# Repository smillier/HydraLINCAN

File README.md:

# HydraLINCAN shield for HydraBus

CAN and LIN Bus shield for Hydrabus http://hydrabus.com/
Refer to Hydrabus Wiki for more information on usage. https://github.com/hydrabus/hydrafw/wiki/HydraFW-CAN-guide

#### New version with cleaner and easier to read silkscreen.

Here is the wiring schema for HydraLINCAN.

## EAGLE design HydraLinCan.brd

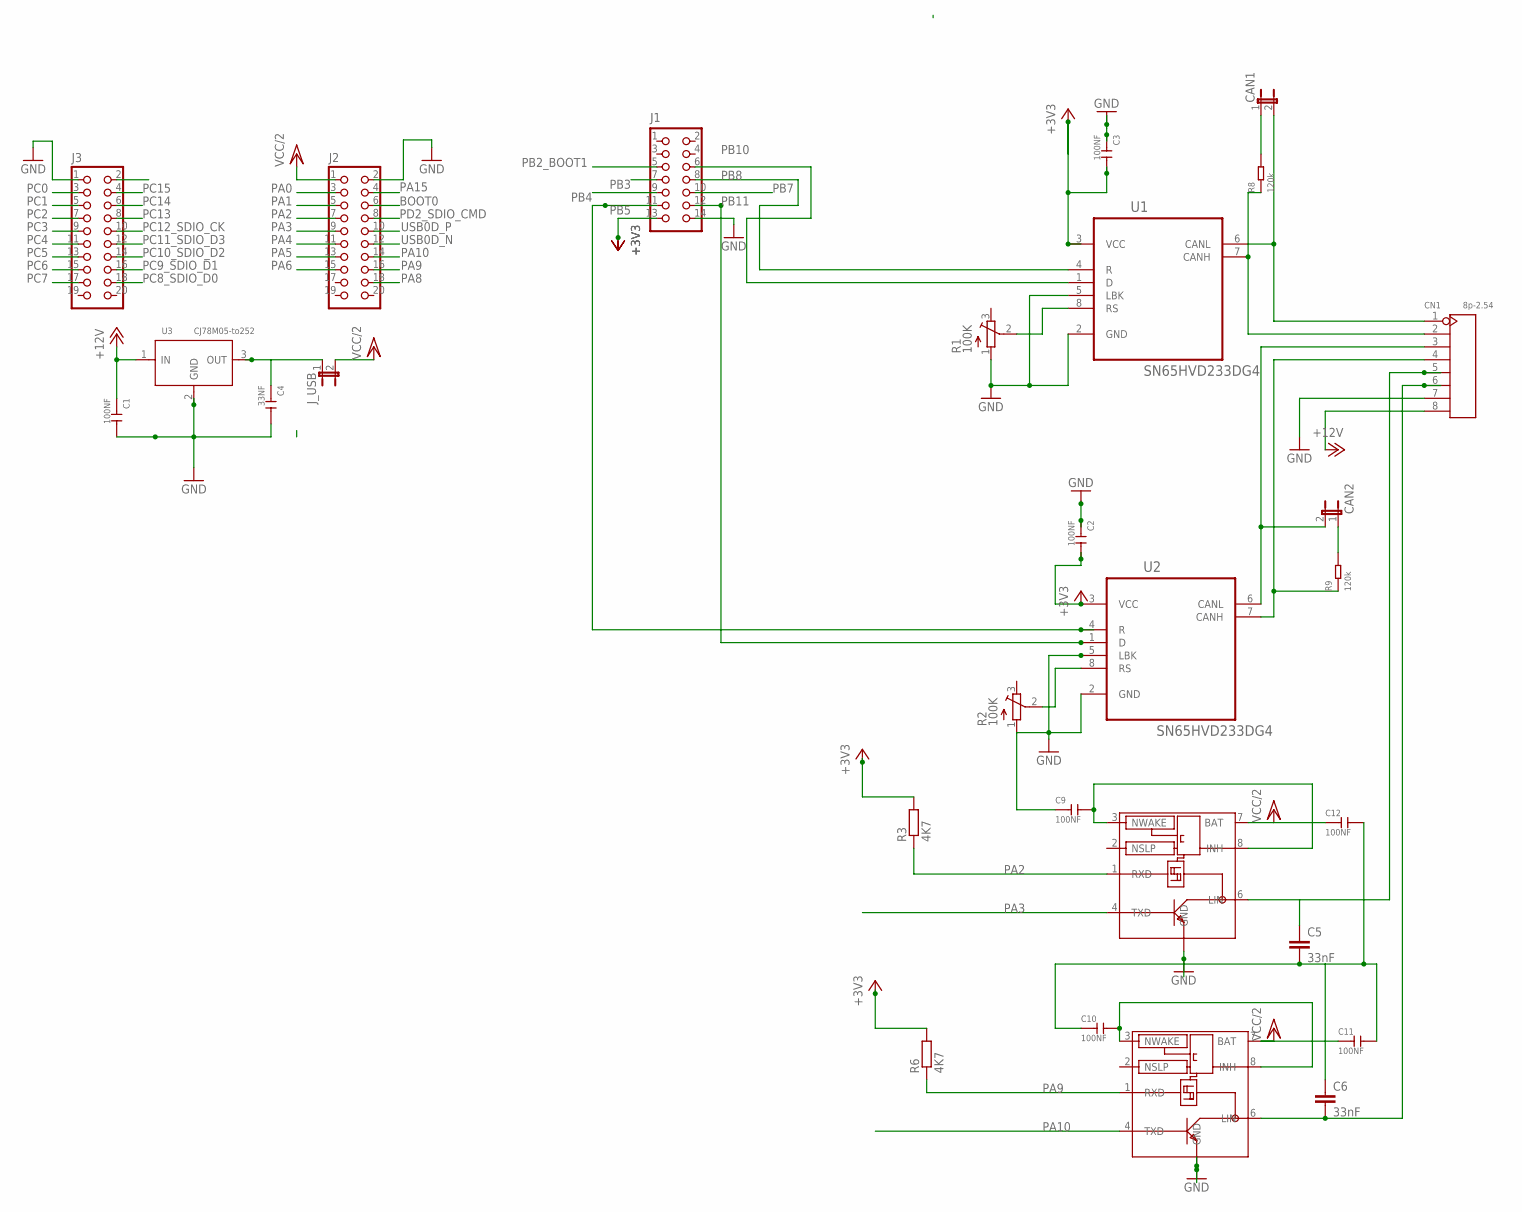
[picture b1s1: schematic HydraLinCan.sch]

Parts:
C1, C2, C3, C9, C10, C11, C12: 100NF; C0805
C4: 33NF; C0805
C5, C6: 33nF; 1206
CAN1, CAN2: JP1E; JP1
CN1: 8p-2.54; H8-2.54
J1: HYDRABUS_SHIELD_CON_HEADER_2X07; HYDRABUS_SHIELD_M2X7
J2, J3: HYDRABUS_SHIELD_CON_HEADER_2X10; HYDRABUS_SHIELD_M2X10
J_USB: JP1E; JP1
LIN1, LIN2: TJA1021SO8; SO8
R1, R2: 100K; SM-42/43A
R3, R6: 4K7; M1206
R8, R9: 120k; R1206
U1, U2: SN65HVD233DG4; SOIC127P600X175-8N
U3: CJ78M05-to252; TO-252

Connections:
+3V3: C2.2, C3.2, J1.13, R3.2, R6.2, U1.3 (VCC), U2.3 (VCC)
+12V: C1.1, CN1.8, U3.1 (IN)
BOOT0: J2.6
CAN1_N: CAN1.2, CN1.1, U1.6 (CANL)
CAN1_P: CN1.2, R8.1, U1.7 (CANH)
CAN2_N: CAN2.2, CN1.3, U2.6 (CANL)
CAN2_P: CN1.4, R9.1, U2.7 (CANH)
GND: C1.2, C2.1, C3.1, C4.2, C5.2, C6.1, C10.1, C11.2, C12.2, CN1.7, J1.14, J2.2, J3.1, LIN1.5 (GND), LIN2.5 (GND), R1.1 (A), U1.2 (GND), U1.5 (LBK), U2.5 (LBK), U3.2 (GND)
unnamed: R1.2 (S), U1.8 (RS)
unnamed: C5.1, CN1.5, LIN1.6 (LIN)
unnamed: C6.2, CN1.6, LIN2.6 (LIN)
unnamed: C9.2, LIN1.3 (NWAKE), LIN1.8 (INH)
unnamed: C10.2, LIN2.3 (NWAKE), LIN2.8 (INH)
unnamed: C9.1, R2.1 (A), U2.2 (GND)
unnamed: C4.1, J_USB.1, U3.3 (OUT)
unnamed: CAN2.1, R9.2
unnamed: R2.2 (S), U2.8 (RS)
unnamed: CAN1.1, R8.2
PA0: J2.3
PA1: J2.5
PA2: J2.7, LIN1.1 (RXD), R3.1
PA3: J2.9, LIN1.4 (TXD)
PA4: J2.11
PA5: J2.13
PA6: J2.15
PA8: J2.18
PA9: J2.16, LIN2.1 (RXD), R6.1
PA10: J2.14, LIN2.4 (TXD)
PA15: J2.4
PB2_BOOT1: J1.5
PB3: J1.7
PB4: J1.9
PB5: J1.11, U2.4 (R)
PB7: J1.10
PB8: J1.8, U1.4 (R)
PB10: J1.6, U1.1 (D)
PB11: J1.12, U2.1 (D)
PC0: J3.3
PC1: J3.5
PC2: J3.7
PC3: J3.9
PC4: J3.11
PC5: J3.13
PC6: J3.15
PC7: J3.17
PC8_SDIO_D0: J3.18
PC9_SDIO_D1: J3.16
PC10_SDIO_D2: J3.14
PC11_SDIO_D3: J3.12
PC12_SDIO_CK: J3.10
PC13: J3.8
PC14: J3.6
PC15: J3.4
PD2_SDIO_CMD: J2.8
USB0D_N: J2.12
USB0D_P: J2.10
VCC/2: C11.1, C12.1, J2.1, J_USB.2, LIN1.7 (BAT), LIN2.7 (BAT)

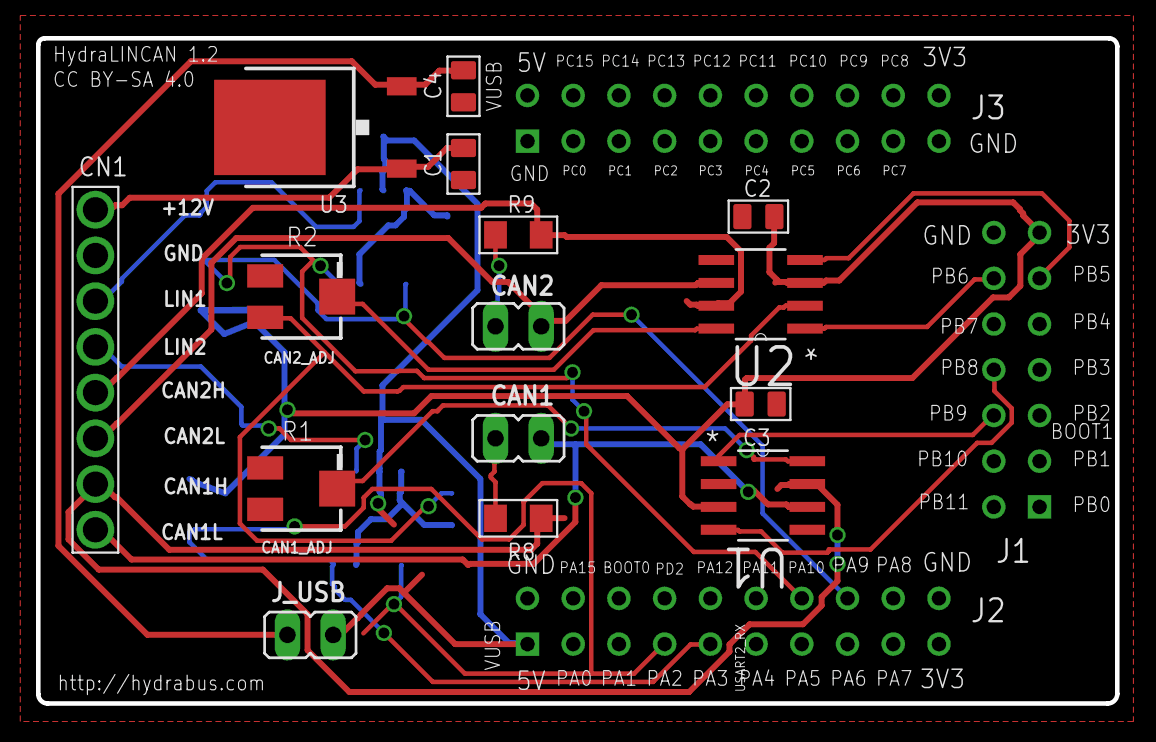
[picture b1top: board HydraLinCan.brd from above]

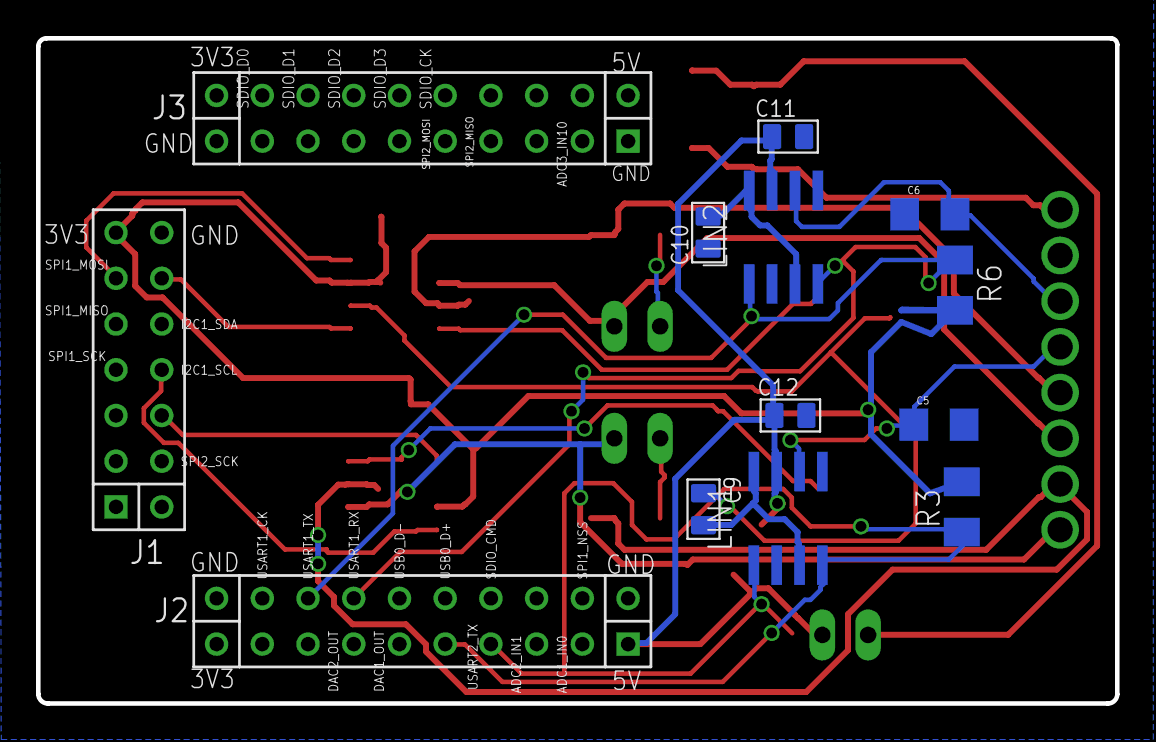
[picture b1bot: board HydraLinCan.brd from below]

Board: 2 copper layers, 59.9 x 37.0 mm, 28 parts (10 on the bottom side), 26 nets.

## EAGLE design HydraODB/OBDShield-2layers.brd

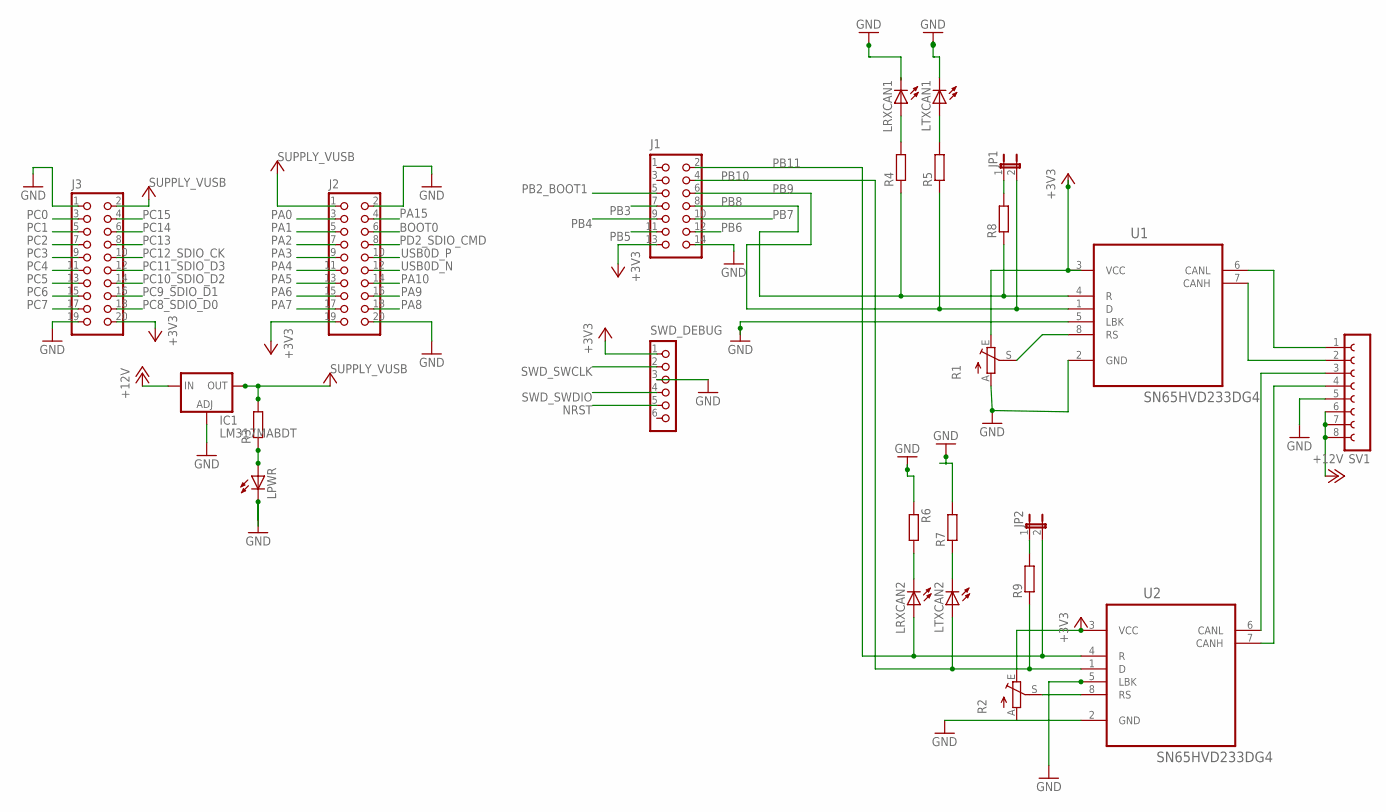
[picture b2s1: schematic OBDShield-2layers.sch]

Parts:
IC1: LM317MABDT; DPACK
J1: HYDRABUS_SHIELD_CON_HEADER_2X07; HYDRABUS_SHIELD_M2X7
J2, J3: HYDRABUS_SHIELD_CON_HEADER_2X10; HYDRABUS_SHIELD_M2X10
JP1, JP2: JP1E; JP1
LPWR: LEDCHIPLED_0603; CHIPLED_0603
LRXCAN1, LRXCAN2: LEDCHIPLED_0603; CHIPLED_0603
LTXCAN1, LTXCAN2: LEDCHIPLED_0603; CHIPLED_0603
R1, R2: TRIM_EU-B25U; B25U
R3, R4, R5, R6, R7, R8, R9: R-EU_R0603; R0603
SV1: FE08-1; FE08
SWD_DEBUG: HYDRABUS_SHIELD_CON_HEADER_1X06; HYDRABUS_SHIELD_M1X6
U1, U2: SN65HVD233DG4; SOIC127P600X175-8N

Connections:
+3V3: J1.13, J2.19, J3.20, R1.E, R2.E, SWD_DEBUG.1, U1.3 (VCC), U2.3 (VCC)
+12V: IC1.3 (IN), SV1.6, SV1.7, SV1.8
BOOT0: J2.6
GND: IC1.1 (ADJ), J1.14, J2.2, J2.20, J3.1, J3.19, LPWR.C, LTXCAN1.C, R1.A, R2.A, R6.1, SV1.5, SWD_DEBUG.3, U1.2 (GND), U1.5 (LBK), U2.2 (GND), U2.5 (LBK)
unnamed: R1.S, U1.8 (RS)
unnamed: LRXCAN2.C, R6.2
unnamed: LTXCAN2.C, R7.1
unnamed: LRXCAN1.A, R4.2
unnamed: SV1.1, U1.6 (CANL)
unnamed: SV1.2, U1.7 (CANH)
unnamed: SV1.3, U2.6 (CANL)
unnamed: SV1.4, U2.7 (CANH)
unnamed: LTXCAN1.A, R5.2
unnamed: LPWR.A, R3.1
unnamed: JP2.1, R9.2
unnamed: R2.S, U2.8 (RS)
unnamed: JP1.1, R8.2
NRST: SWD_DEBUG.5
PA0: J2.3
PA1: J2.5
PA2: J2.7
PA3: J2.9
PA4: J2.11
PA5: J2.13
PA6: J2.15
PA7: J2.17
PA8: J2.18
PA9: J2.16
PA10: J2.14
PA15: J2.4
PB2_BOOT1: J1.5
PB3: J1.7
PB4: J1.9
PB5: J1.11
PB6: J1.12
PB7: J1.10
PB8: J1.8, R4.1, R8.1, U1.4 (R)
PB9: J1.2, JP2.2, LRXCAN2.A, U2.4 (R)
PB10: J1.6, JP1.2, R5.1, U1.1 (D)
PB11: J1.4, LTXCAN2.A, R9.1, U2.1 (D)
PC0: J3.3
PC1: J3.5
PC2: J3.7
PC3: J3.9
PC4: J3.11
PC5: J3.13
PC6: J3.15
PC7: J3.17
PC8_SDIO_D0: J3.18
PC9_SDIO_D1: J3.16
PC10_SDIO_D2: J3.14
PC11_SDIO_D3: J3.12
PC12_SDIO_CK: J3.10
PC13: J3.8
PC14: J3.6
PC15: J3.4
PD2_SDIO_CMD: J2.8
SWD_SWCLK: SWD_DEBUG.2
SWD_SWDIO: SWD_DEBUG.4
USB0D_N: J2.12
USB0D_P: J2.10
VUSB: IC1.4 (OUT), J2.1, J3.2

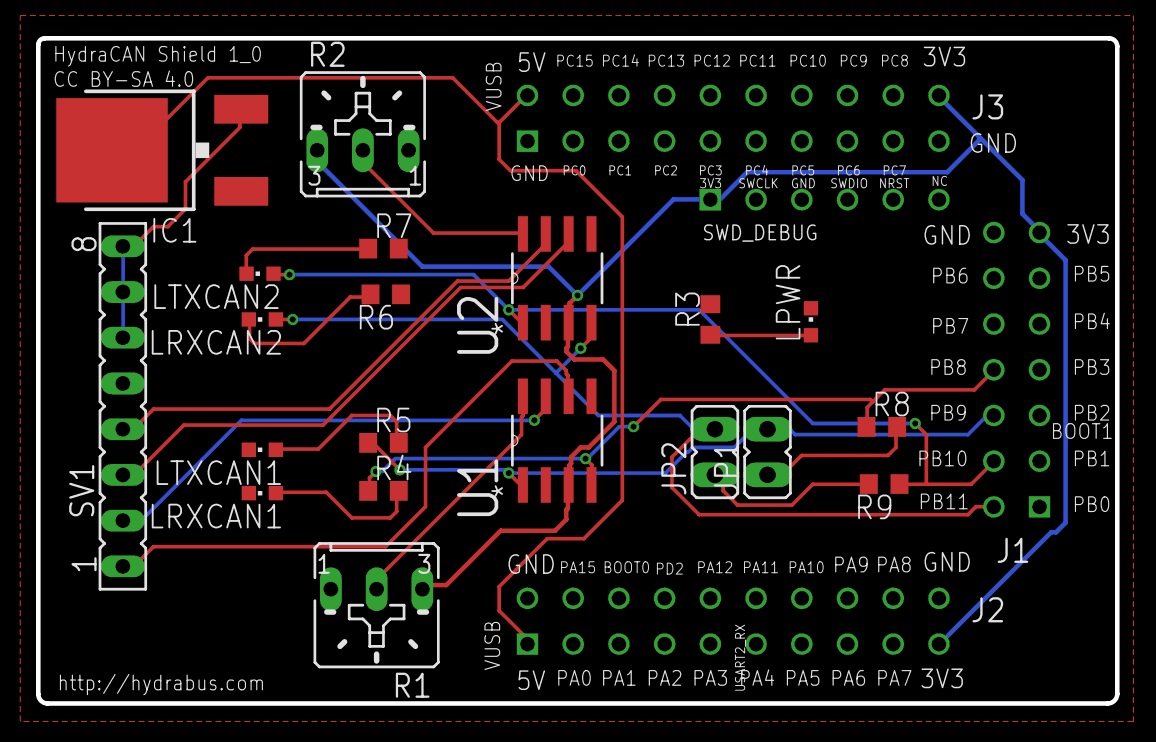
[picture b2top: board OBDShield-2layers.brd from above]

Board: 2 copper layers, 59.9 x 37.0 mm, 24 parts (0 on the bottom side), 21 nets.

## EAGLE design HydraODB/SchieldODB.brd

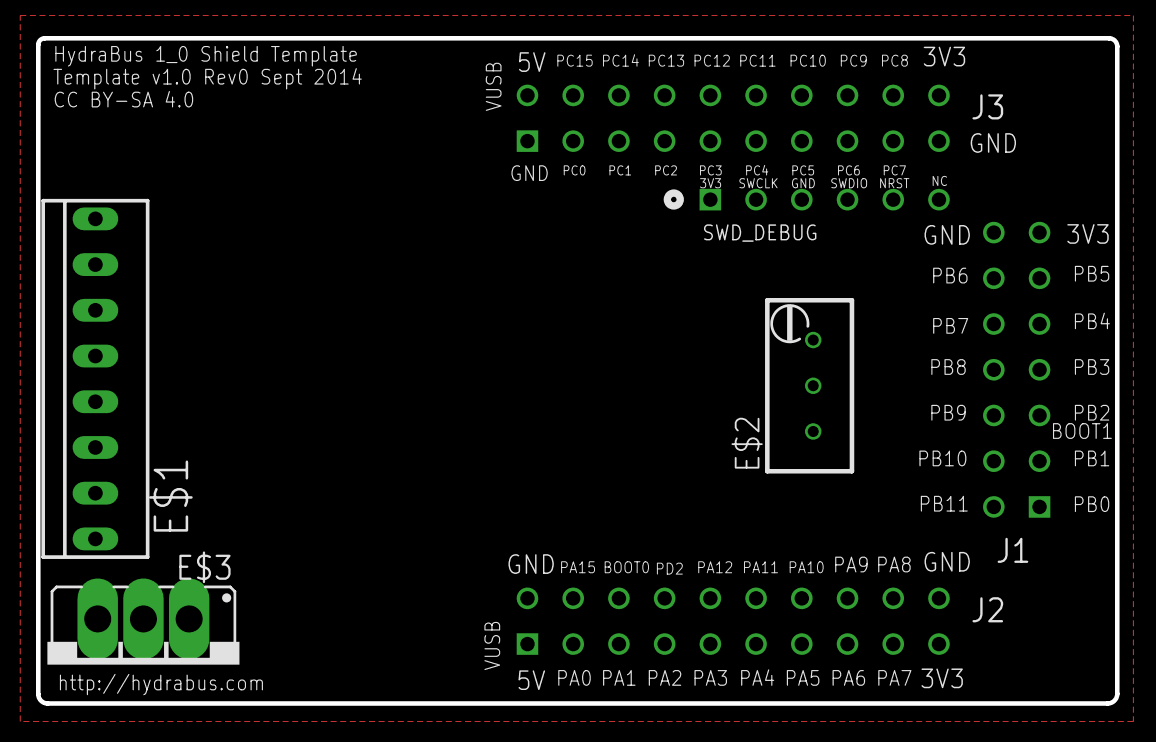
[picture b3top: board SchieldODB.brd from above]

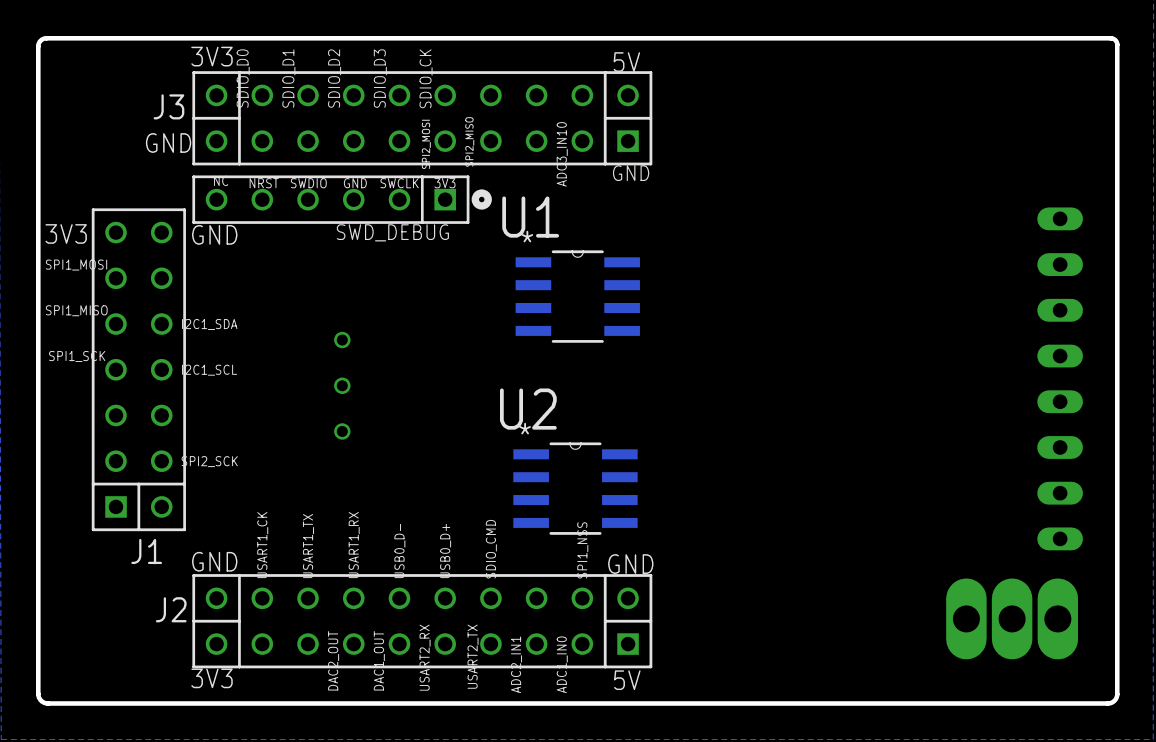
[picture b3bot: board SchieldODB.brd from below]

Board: 2 copper layers, 59.9 x 37.0 mm, 9 parts (2 on the bottom side), 3 nets, no tracks yet.

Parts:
E$1: 741256-49
E$2: RTRIMT93YA
E$3: 79XXS_
J1: HYDRABUS_SHIELD_CON_HEADER_2X07; HYDRABUS_SHIELD_M2X7
J2, J3: HYDRABUS_SHIELD_CON_HEADER_2X10; HYDRABUS_SHIELD_M2X10
SWD_DEBUG: HYDRABUS_SHIELD_CON_HEADER_1X06; HYDRABUS_SHIELD_M1X6
U1, U2: SN65HVD233D; SOIC127P600X175-8N

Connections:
+3V3: J1.13, J2.19, J3.20, SWD_DEBUG.1, U2.3
GND: J1.14, J2.2, J2.20, J3.1, J3.19, SWD_DEBUG.3, U1.2, U1.8, U2.2, U2.8
VUSB: J2.1, J3.2

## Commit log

2015-08-26 :lollipop: Added .gitattributes & .gitignore files
2015-08-27 Eagle Project
2015-09-03 Schema and board corrections
2015-09-03 Remove history files
2015-09-16 VReg add, CanBus 2 rewired
2015-09-16 Schema redisign
2015-10-07 Rebuilt everything, schema and board were inconsistent. First try at PCB routing.
2015-10-07 board pcb routing tryout
2015-10-12 Placing and routing
2015-10-13 Proto pcb routing
    Routing signle layer for proto pcb
2015-10-13 Schema correction
2015-10-16 2 Layers PCB
2015-10-16 File move
2015-11-17 Corrected J2 mirror
2015-11-17 Upload gerber for 1 layer pcb
2015-11-19 CleanUp - Start over from 2 layers shield
2015-11-19 Mistake :-D
2015-11-19 Decoupling caps, user button and different mistakes
2015-11-22 GBR updated
2015-11-24 Different corrections and missing wire
2015-11-25 Decap condos
2015-11-30 Updated board
2016-02-22 Board modifications, silk screen
    Still some work to do on the board
2016-02-23 Solved files merging pb.
2016-02-24 Power changed and jumper added, packages changed, inverted can h/l on silk
2016-02-24 Shield 3D preview
2016-02-24 Updated 3D preview
2016-02-28 OBD Connector corrected, VReg changed, Routing modification and smd packages corrected
2016-06-07 final working routing,
2016-06-10 Final
2017-03-30 Added 2 LIN Bus transceivers
2017-03-31 PCB preview
2017-03-31 Pullups for LIN transceivers
2017-05-03 Routing corrections
2017-05-04 corrections on ground plate
2017-07-05 Added picture of finished product
2017-08-29 Corrections for CAN and LIN buses
    Deleted connections between trimmers and VCC
    Added decap on LIN tranceivers
2017-09-04 routing improvements
    Via size increased, manual can traces routes, decap routed correctly. Should be ready for fab, BOM still to come
2017-10-05 Routing corrections + Mouser BOM
2017-11-08 BOM Optimazation and DigiKey Refs
    BOM Optimazation and DigiKey Refs
2018-01-19 Wiring HydraLINCAN board
2018-01-19 Update wiring schema
2019-08-25 Add LCSC parts
2020-02-03 2 layers parts
2020-02-03 Routing CAN H/L as real diff pairs
2020-02-03 New version Fusion360 3D preview
    Cleaner design
2020-02-11 Silkscreen cleaning
2020-02-11 3DPreview
2020-02-12 Typo 120K -> 120 bus termination resistor
2023-01-11 Upgrade LIN transceivers for LIN2.0-2.2A/SAE J2602 and ISO 17984-4 compatibility

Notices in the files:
HydraLinCan.brd:
CC BY-SA 4.0
